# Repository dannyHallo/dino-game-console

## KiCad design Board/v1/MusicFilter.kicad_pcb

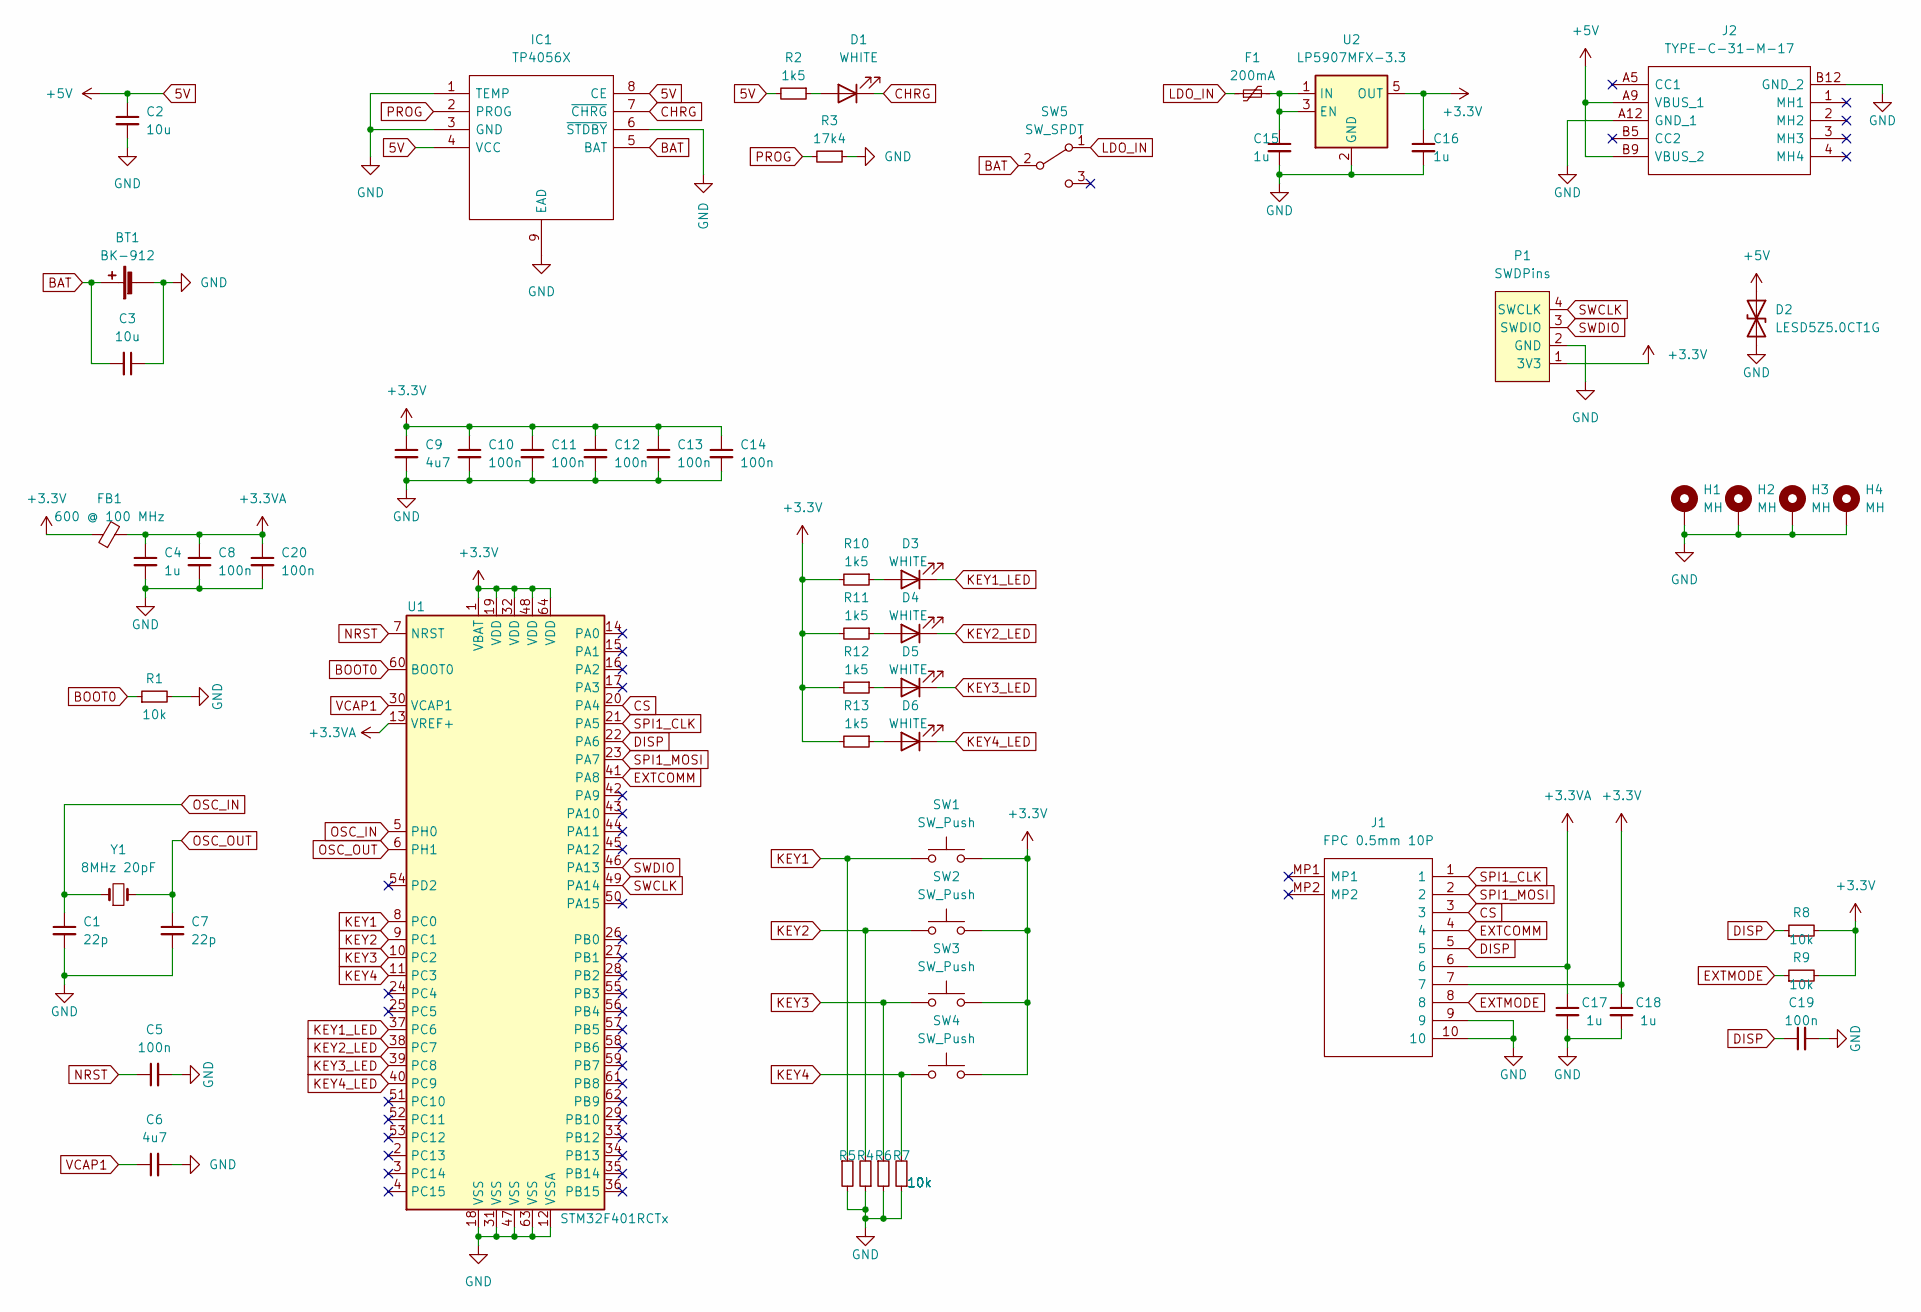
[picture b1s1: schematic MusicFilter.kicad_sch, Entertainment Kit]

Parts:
BT1: BK-912
C1, C7: 22p; C_0603_1608Metric_Pad1.08x0.95mm_HandSolder
C2, C3: 10u; C_0603_1608Metric_Pad1.08x0.95mm_HandSolder
C4, C15, C16, C17, C18: 1u; C_0603_1608Metric_Pad1.08x0.95mm_HandSolder
C5, C8, C10, C11, C12, C13, C14, C19, C20: 100n; C_0603_1608Metric_Pad1.08x0.95mm_HandSolder
C6, C9: 4u7; C_0603_1608Metric_Pad1.08x0.95mm_HandSolder
D1, D3, D4, D5, D6: WHITE; LED_0805_2012Metric_Pad1.15x1.40mm_HandSolder
D2: LESD5Z5.0CT1G; D_SOD-523
F1: 200mA; Fuse_0603_1608Metric_Pad1.05x0.95mm_HandSolder
FB1: 600 @ 100 MHz; L_0603_1608Metric_Pad1.05x0.95mm_HandSolder
H1, H2, H3, H4: MH; MountingHole_2.2mm_M2_Pad_Via
IC1: TP4056X; ESOP-8_L4.9-W3.9-P1.27-LS6.0-BL-EP; Manufacturer_Part_Number TP4056X
J1: FPC 0.5mm 10P; 96x96 Sharp Memory Lcd With FPC Connector 10p 0.5mm; Manufacturer_Part_Number 1-1734839-0; Mouser Part Number 571-1-1734839-0
J2: TYPE-C-31-M-17; TYPE-C-SMD_TYPE-C-31-M-16; Manufacturer_Part_Number TYPE-C-31-M-17
P1: SWDPins; 4X1_PROGRAM_PIN
R1, R4, R5, R6, R7, R8, R9: 10k; R_0603_1608Metric_Pad0.98x0.95mm_HandSolder
R2, R10, R11, R12, R13: 1k5; R_0603_1608Metric_Pad0.98x0.95mm_HandSolder
R3: 17k4; R_0603_1608Metric_Pad0.98x0.95mm_HandSolder
SW1, SW2, SW3, SW4: SW_Push; SW_Kailh_Choc_V1_HOTSWAP
SW5: SW_SPDT; SW_SPDT_PCM12
U1: STM32F401RCTx; LQFP-64_10x10mm_P0.5mm
U2: LP5907MFX-3.3; SOT-23-5
Y1: 8MHz 20pF; Crystal_SMD_5032-2Pin_5.0x3.2mm_HandSoldering

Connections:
5V: C2.1, D2.1 (A1), IC1.4 (VCC), IC1.8 (CE), J2.A9 (VBUS_1), J2.B9 (VBUS_2), R2.2
+3.3VA: C4.1, C8.1, C17.1, C20.1, FB1.2, J1.6, U1.13 (VREF+)
+3V3: C9.1, C10.1, C11.1, C12.1, C13.1, C14.1, C16.1, C18.1, FB1.1, J1.7, P1.1 (3V3), R8.2, R9.2, R10.2, R11.2, R12.2, R13.2, SW1.2, SW2.2, SW3.2, SW4.2, U1.1 (VBAT), U1.19 (VDD), U1.32 (VDD), U1.48 (VDD), U1.64 (VDD), U2.5 (OUT)
BAT: BT1.1 (+), C3.2, IC1.5 (BAT), SW5.2 (B)
BOOT0: R1.1, U1.60 (BOOT0)
CHRG: D1.1 (K), IC1.7 (~CHRG)
CS: J1.3, U1.20 (PA4)
DISP: C19.1, J1.5, R8.1, U1.22 (PA6)
EXTCOMM: J1.4, U1.41 (PA8)
EXTMODE: J1.8, R9.1
GND: BT1.2 (-), C1.2, C2.2, C3.1, C4.2, C5.2, C6.2, C7.2, C8.2, C9.2, C10.2, C11.2, C12.2, C13.2, C14.2, C15.2, C16.2, C17.2, C18.2, C19.2, C20.2, D2.2 (A2), H1.1, H2.1, H3.1, H4.1, IC1.1 (TEMP), IC1.3 (GND), IC1.6 (~STDBY), IC1.9 (EAD), J1.9, J1.10, J2.A12 (GND_1), J2.B12 (GND_2), P1.2 (GND), R1.2, R3.1, R4.2, R5.1, R6.2, R7.1, U1.12 (VSSA), U1.18 (VSS), U1.31 (VSS), U1.47 (VSS), U1.63 (VSS), U2.2 (GND)
KEY1: R4.1, SW1.1, U1.8 (PC0)
KEY1_LED: D3.1 (K), U1.37 (PC6)
KEY2: R5.2, SW2.1, U1.9 (PC1)
KEY2_LED: D4.1 (K), U1.38 (PC7)
KEY3: R6.1, SW3.1, U1.10 (PC2)
KEY3_LED: D5.1 (K), U1.39 (PC8)
KEY4: R7.2, SW4.1, U1.11 (PC3)
KEY4_LED: D6.1 (K), U1.40 (PC9)
LDO_IN: F1.1, SW5.1 (A)
NRST: C5.1, U1.7 (NRST)
unnamed: C15.1, F1.2, U2.1 (IN), U2.3 (EN)
unnamed: D1.2 (A), R2.1
unnamed: D3.2 (A), R10.1
unnamed: D4.2 (A), R11.1
unnamed: D5.2 (A), R12.1
unnamed: D6.2 (A), R13.1
OSC_IN: C1.1, U1.5 (PH0), Y1.1
OSC_OUT: C7.1, U1.6 (PH1), Y1.2
PROG: IC1.2 (PROG), R3.2
SPI1_CLK: J1.1, U1.21 (PA5)
SPI1_MOSI: J1.2, U1.23 (PA7)
SWCLK: P1.4 (SWCLK), U1.49 (PA14)
SWDIO: P1.3 (SWDIO), U1.46 (PA13)
VCAP1: C6.1, U1.30 (VCAP1)

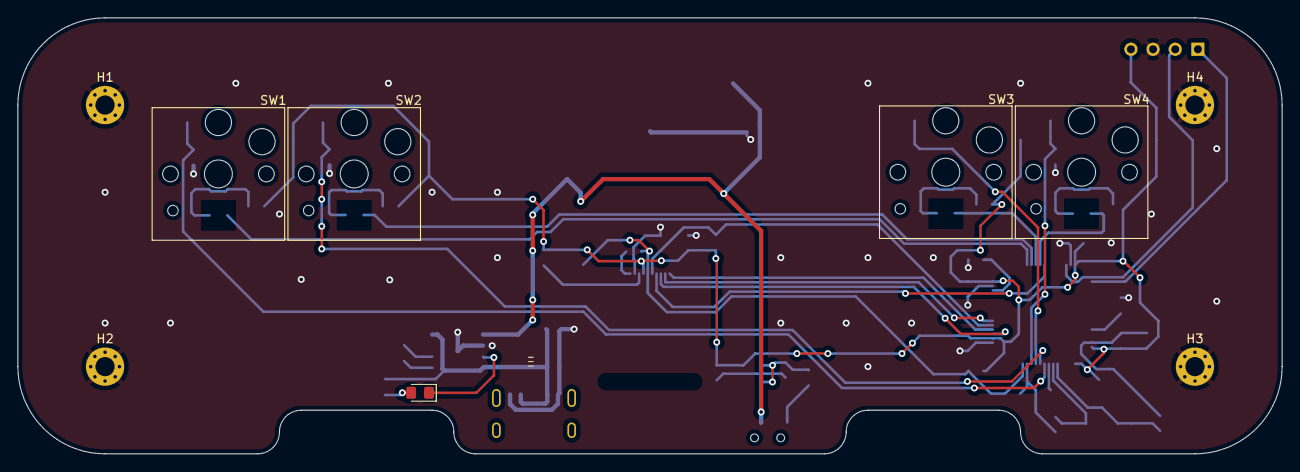
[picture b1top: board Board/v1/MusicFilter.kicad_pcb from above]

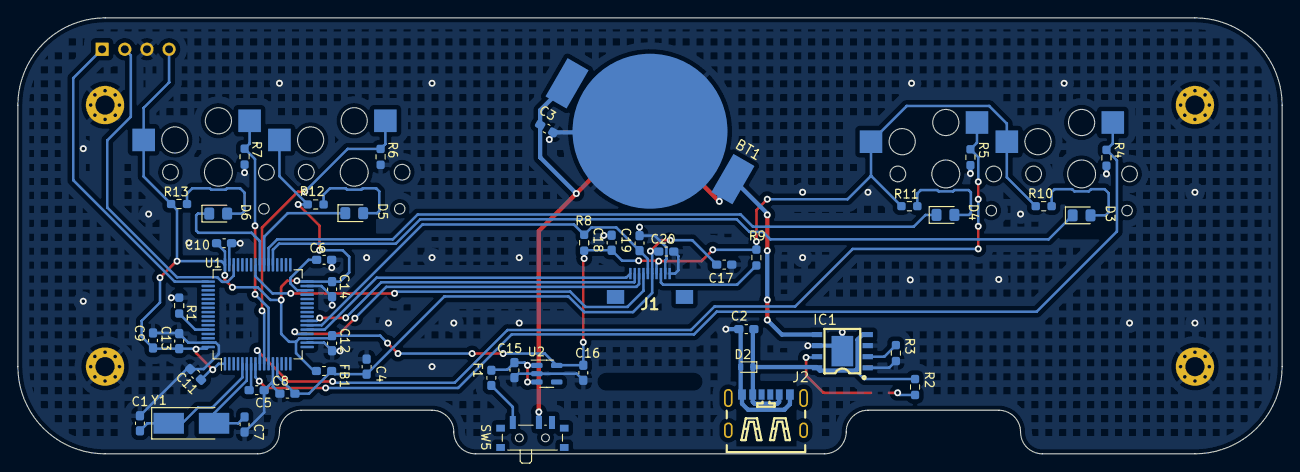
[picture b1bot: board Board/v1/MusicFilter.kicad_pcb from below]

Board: 2 copper layers, 145.0 x 50.0 mm, 58 parts (48 on the bottom side), 35 nets.

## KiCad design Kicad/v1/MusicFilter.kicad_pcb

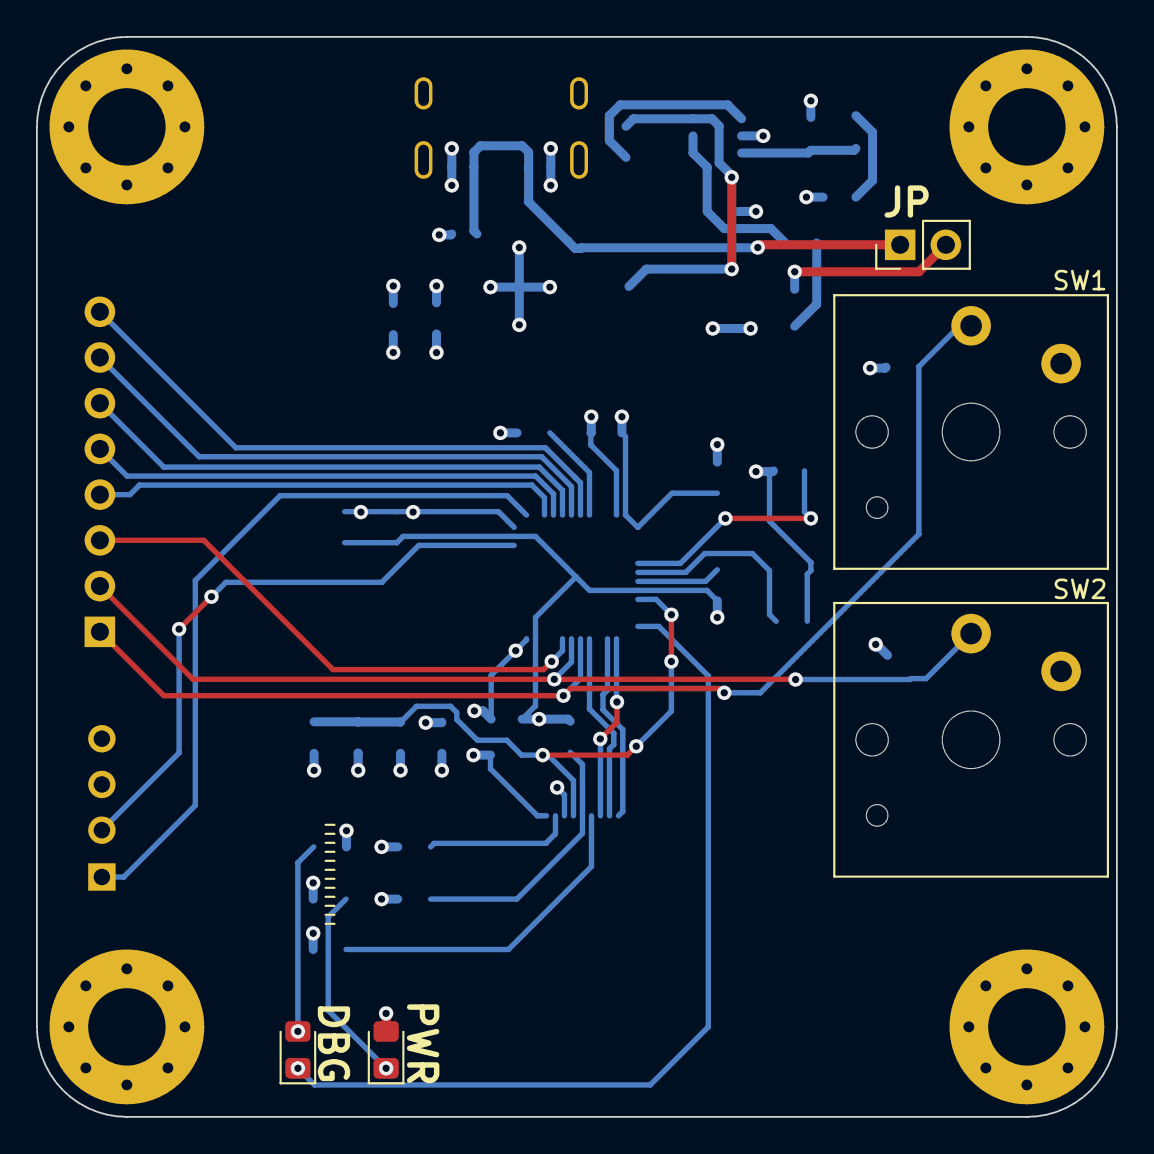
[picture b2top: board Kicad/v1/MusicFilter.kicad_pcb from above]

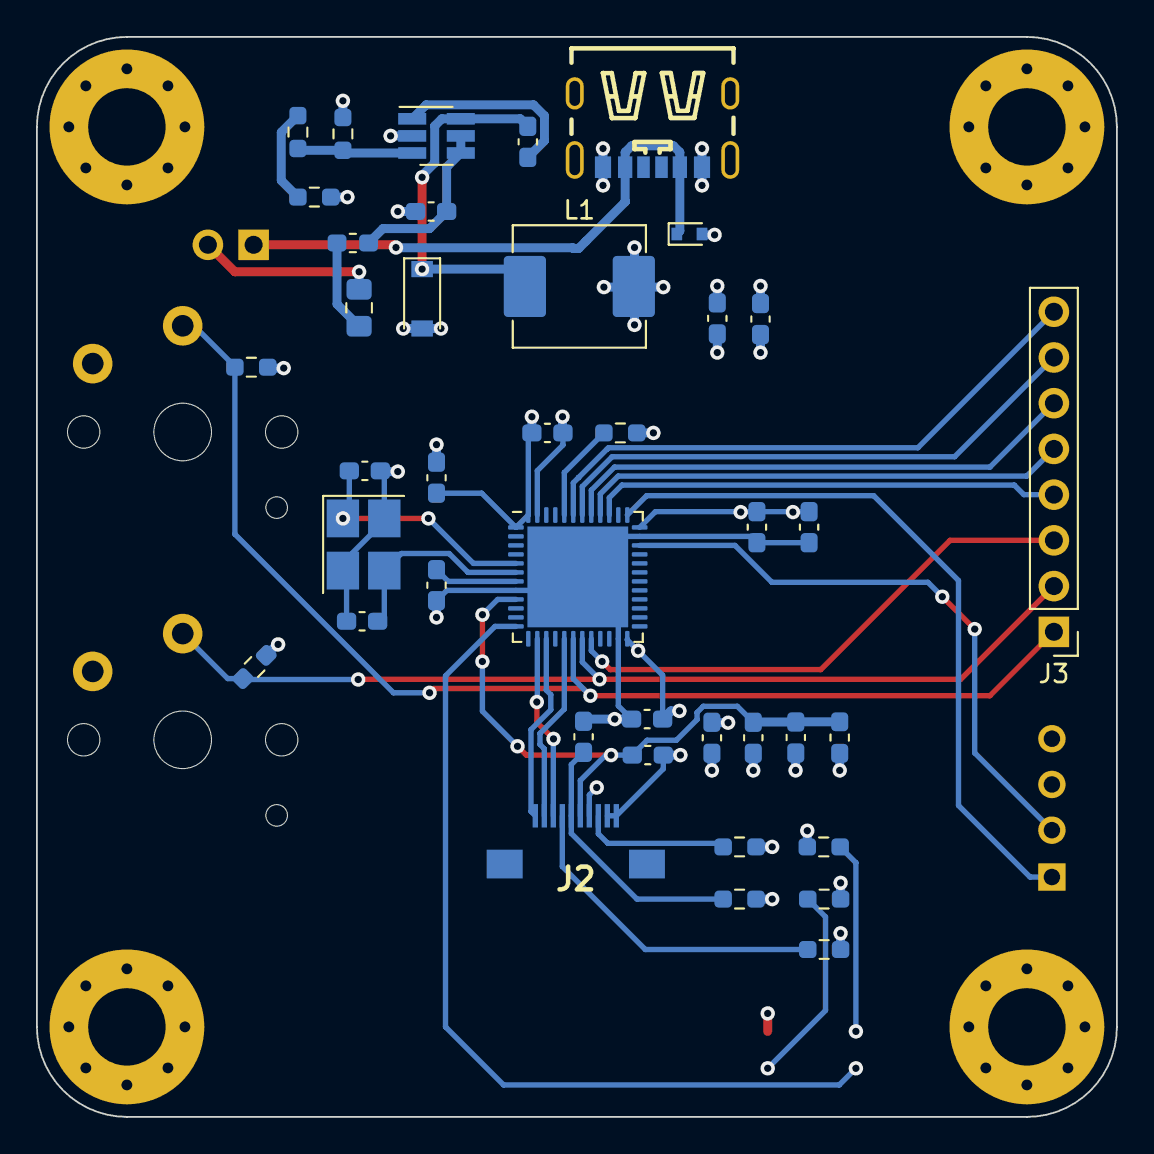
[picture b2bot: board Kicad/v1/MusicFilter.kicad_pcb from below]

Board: 4 copper layers, 60.0 x 60.0 mm, 51 parts (41 on the bottom side), 34 nets.

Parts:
C1, C11: 10n; C_0603_1608Metric_Pad1.08x0.95mm_HandSolder
C2, C3, C4: 10u; C_0603_1608Metric_Pad1.08x0.95mm_HandSolder
C5: 4u7; C_0603_1608Metric_Pad1.08x0.95mm_HandSolder
C6, C7, C8, C9, C12, C17: 100n; C_0603_1608Metric_Pad1.08x0.95mm_HandSolder
C10, C13, C14: 1u; C_0603_1608Metric_Pad1.08x0.95mm_HandSolder
C15, C16: 12p; C_0603_1608Metric_Pad1.08x0.95mm_HandSolder
D1: B5819W; D_SOD-123
D2: LESD5Z5.0CT1G; D_SOD-523
D3: RED; LED_0805_2012Metric_Pad1.15x1.40mm_HandSolder
D4: BLUE; LED_0805_2012Metric_Pad1.15x1.40mm_HandSolder
DECO**: Val**; FOR_TEST
F1: 500mA; Fuse_0805_2012Metric_Pad1.15x1.40mm_HandSolder
FB1, FB2: 600 @ 100 MHz; L_0603_1608Metric_Pad1.05x0.95mm_HandSolder
H1, H2, H3, H4: MountingHole_Pad; MountingHole_4.3mm_M4_Pad_Via
J1: TYPE-C-31-M-17; TYPE-C-SMD_TYPE-C-31-M-16
J2: FPC 0.5mm 10P
J3: Conn_01x08_Male; PinHeader_1x08_P2.54mm_Vertical
J4: Conn_01x02_Male; PinHeader_1x02_P2.54mm_Vertical
L1: 47u; L_Abracon_ASPI-0630LR
P1: SWDPins; 4X1_PROGRAM_PIN
R1, R4, R6, R7, R8, R10, R11: 10k; R_0603_1608Metric_Pad0.98x0.95mm_HandSolder
R2: 15k; R_0603_1608Metric_Pad0.98x0.95mm_HandSolder
R3: 270; R_0603_1608Metric_Pad0.98x0.95mm_HandSolder
R5: 1k5; R_0603_1608Metric_Pad0.98x0.95mm_HandSolder
R9: 1k; R_0603_1608Metric_Pad0.98x0.95mm_HandSolder
SW1, SW2: SW_Push; SW_Kailh_Choc_V1
U1: MP2359; SOT-23-6_Handsoldering
U2: STM32F103CBUx; QFN-48-1EP_7x7mm_P0.5mm_EP5.6x5.6mm
Y1: 8MHz; Crystal_SMD_3225-4Pin_3.2x2.5mm_HandSoldering

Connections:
+3.3VA: C10.1, C11.1, C13.1, FB2.2, J2.6, U2.9 (VDDA)
+3V3: C3.2, C4.2, C5.1, C6.1, C7.1, C8.1, C9.1, C14.1, D3.2 (A), FB2.1, J2.7, L1.2, P1.1 (3V3), R1.2, R4.2, R9.2, SW1.2, SW2.2, U2.1 (VBAT), U2.24 (VDD), U2.36 (VDD), U2.48 (VDD)
+5V: D2.1 (A1), J1.A9 (VBUS_1), J1.B9 (VBUS_2), J4.1
/KEY1: J3.1, R10.1, SW1.1, U2.18 (PB0)
/KEY2: J3.2, R11.2, SW2.1, U2.19 (PB1)
BOOT0: R8.1, U2.44 (BOOT0)
BUCK_BST: C1.2, U1.1 (BST)
BUCK_EN: C2.1, FB1.2, U1.4 (EN), U1.5 (IN)
BUCK_FB: R1.1, R2.2, U1.3 (FB)
BUCK_SW: C1.1, D1.1 (K), L1.1, U1.6 (SW)
CS: J2.3, U2.14 (PA4)
DISP: C12.1, J2.5, R4.1
EXTCOMM: J2.4, R6.1
EXTMODE: J2.8, R7.1
GND: C2.2, C3.1, C4.1, C5.2, C6.2, C7.2, C8.2, C9.2, C10.2, C11.2, C12.2, C13.2, C14.2, C15.2, C16.2, C17.2, D1.2 (A), D2.2 (A2), H1.1, H2.1, H3.1, H4.1, J1.A12 (GND_1), J1.B12 (GND_2), J2.9, J2.10, P1.2 (GND), R3.1, R5.1, R6.2, R7.2, R8.2, R10.2, R11.1, U1.2 (GND), U2.8 (VSSA), U2.23 (VSS), U2.35 (VSS), U2.47 (VSS), U2.49 (VSS), Y1.2, Y1.4
LED_STATUS: D4.1 (K), U2.12 (PA2)
NRST: C17.1, U2.7 (NRST)
unnamed: D3.1 (K), R5.2
unnamed: D4.2 (A), R9.1
unnamed: F1.1, J4.2
unnamed: F1.2, FB1.1
unnamed: R2.1, R3.2
unnamed: J3.3, U2.20 (PB2)
unnamed: J3.4, U2.39 (PB3)
unnamed: J3.5, U2.40 (PB4)
unnamed: J3.6, U2.41 (PB5)
unnamed: J3.7, U2.42 (PB6)
unnamed: J3.8, U2.43 (PB7)
OSC_IN: C15.1, U2.5 (PD0), Y1.1
OSC_OUT: C16.1, U2.6 (PD1), Y1.3
SPI1_CLK: J2.1, U2.15 (PA5)
SPI1_MOSI: J2.2, U2.17 (PA7)
SWCLK: P1.4 (SWCLK), U2.37 (PA14)
SWDIO: P1.3 (SWDIO), U2.34 (PA13)

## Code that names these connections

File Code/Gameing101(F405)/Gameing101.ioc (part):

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Mcu.Name=STM32F401R(B-C)Tx
Mcu.Package=LQFP64
Mcu.UserName=STM32F401RCTx
PA13.Mode=Serial_Wire
PA13.Signal=SYS_JTMS-SWDIO
PA14.Mode=Serial_Wire
PA14.Signal=SYS_JTCK-SWCLK
PA4.GPIOParameters=GPIO_Label
PA4.GPIO_Label=CS
PA4.Signal=GPIO_Output
PA5.Mode=TX_Only_Simplex_Unidirect_Master
PA5.Signal=SPI1_SCK
PA6.GPIOParameters=PinState,GPIO_Label
PA6.GPIO_Label=DISP
PA6.PinState=GPIO_PIN_SET
PA6.Signal=GPIO_Output
PA7.Mode=TX_Only_Simplex_Unidirect_Master
PA7.Signal=SPI1_MOSI
PA8.GPIOParameters=GPIO_Label
PA8.GPIO_Label=COMM
PA8.Signal=GPIO_Output
PC0.GPIOParameters=GPIO_Label
PC0.GPIO_Label=KEY1
PC0.Signal=GPIO_Input
PC1.GPIOParameters=GPIO_Label
PC1.GPIO_Label=KEY2
PC1.Signal=GPIO_Input
PC2.GPIOParameters=GPIO_Label
PC2.GPIO_Label=KEY3
PC2.Signal=GPIO_Input
PC3.GPIOParameters=GPIO_Label
PC3.GPIO_Label=KEY4
PC3.Signal=GPIO_Input
PC6.GPIOParameters=PinState,GPIO_Label
PC6.GPIO_Label=KEY1_LED
PC6.PinState=GPIO_PIN_SET
PC6.Signal=GPIO_Output
PC7.GPIOParameters=PinState,GPIO_Label
PC7.GPIO_Label=KEY2_LED
PC7.PinState=GPIO_PIN_SET
PC7.Signal=GPIO_Output
PC8.GPIOParameters=PinState,GPIO_Label
PC8.GPIO_Label=KEY3_LED
PC8.PinState=GPIO_PIN_SET
PC8.Signal=GPIO_Output
PC9.GPIOParameters=PinState,GPIO_Label
PC9.GPIO_Label=KEY4_LED
PC9.PinState=GPIO_PIN_SET
PC9.Signal=GPIO_Output
PH0\ -\ OSC_IN.Mode=HSE-External-Oscillator
PH0\ -\ OSC_IN.Signal=RCC_OSC_IN
PH1\ -\ OSC_OUT.Mode=HSE-External-Oscillator
PH1\ -\ OSC_OUT.Signal=RCC_OSC_OUT
RCC.HSE_VALUE=8000000
RCC.SYSCLKFreq_VALUE=72000000
RCC.SYSCLKSource=RCC_SYSCLKSOURCE_PLLCLK
board=custom

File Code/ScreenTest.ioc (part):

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Mcu.Name=STM32F103CBUx
Mcu.Package=UFQFPN48
Mcu.UserName=STM32F103CBUx
PA13.Mode=Trace_Asynchronous_SW
PA13.Signal=SYS_JTMS-SWDIO
PA14.Mode=Trace_Asynchronous_SW
PA14.Signal=SYS_JTCK-SWCLK
PA2.GPIOParameters=PinState,GPIO_Label
PA2.GPIO_Label=LED_B
PA2.PinState=GPIO_PIN_SET
PA2.Signal=GPIO_Output
PA4.GPIOParameters=GPIO_Label
PA4.GPIO_Label=CS
PA4.Signal=GPIO_Output
PA5.Mode=TX_Only_Simplex_Unidirect_Master
PA5.Signal=SPI1_SCK
PA7.Mode=TX_Only_Simplex_Unidirect_Master
PA7.Signal=SPI1_MOSI
PB0.GPIOParameters=GPIO_Label
PB0.GPIO_Label=KEY0
PB0.Signal=GPIO_Input
PB1.GPIOParameters=GPIO_Label
PB1.GPIO_Label=KEY1
PB1.Signal=GPIO_Input
PB3.Mode=Trace_Asynchronous_SW
PB3.Signal=SYS_JTDO-TRACESWO
RCC.SYSCLKFreq_VALUE=32000000
RCC.SYSCLKSource=RCC_SYSCLKSOURCE_PLLCLK
board=custom

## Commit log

2022-04-16 repeat mode
2022-04-16 OverlapDetection
2022-04-19 Added object system, random gen awaits!
2022-04-21 Ram management
2022-04-21 Playable..
2022-04-22 Bugs fixed
2022-04-22 Able to draw circle
2022-04-25 Added font manager
2022-04-26 text spacing, button.h
2022-04-26 PressStartStandard96
2022-04-27 Start & End
2022-05-06 board v2 is out
2022-05-10 F4 supported
    current 20mA to 12mA
2022-05-10 Fire leftover effect, advanced key management
2022-05-10 Lava
2022-05-14 Image index supported
2022-05-14 FadePlants
2022-05-14 Real Gravity Jump
2022-05-14 Parachute
2022-05-15 Minor
2022-05-15 Ground tex
2022-05-15 Fixes
2022-05-17 Various dead textures
2022-05-18 Bird signs
2022-05-19 Flipped
2022-05-21 Statement -> two buttons
2022-05-22 no more lava stuff
2022-05-28 something?
2022-05-30 Added transform
    Improved object management
